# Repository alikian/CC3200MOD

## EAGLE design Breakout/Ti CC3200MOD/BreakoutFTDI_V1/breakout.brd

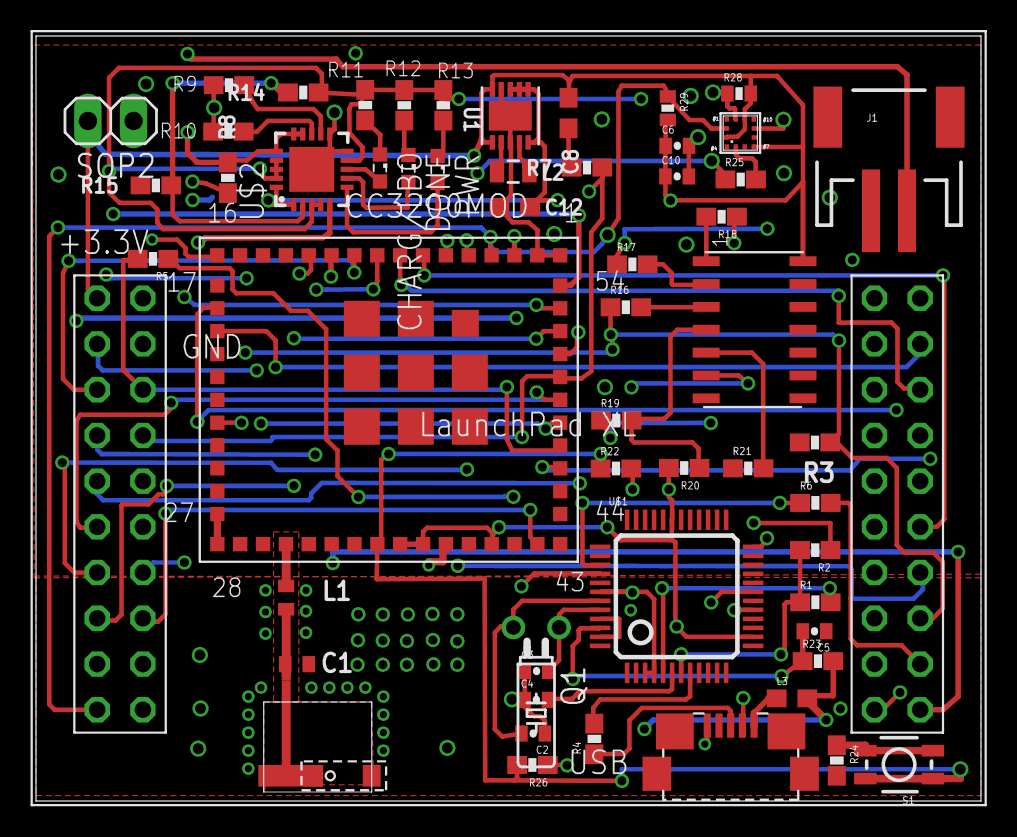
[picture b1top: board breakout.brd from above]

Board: 4 copper layers, 52.5 x 42.5 mm, 57 parts (1 on the bottom side), 66 nets.

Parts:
ANT_PAD: ANT
C1: 1pF; C0402
C2, C3: 27pF; 0402-CAP
C4: 33nF; 0402-CAP
C5: 0.1uF; 0402-CAP
C6, C10: .1uF; 0402-CAP
C8, C12: 10uF; C0603
CC3200MOD: CC3200; CC3200MOD
CHARG/LBO: SML0603
DONE: SML0603
J1: JST-2-SMD
L1: 3.6nH; C0402
L2: 2.2uH; 0805
L3: 0603
PWR: SML0603
Q1: 16Mhz; TC26H
R1: 1.5K; 0603-RES
R2, R4: 28; 0603-RES
R3: 2.7K; 0603-RES
R5, R6, R16, R17, R18, R19, R21, R22, R24: 33; 0603-RES
R7, R10, R26: 100K; 0603-RES
R8: 470K; 0603-RES
R9: 2K; 0603-RES
R11, R12, R13, R14, R15: 1K; 0603-RES
R20: 10k; 0603-RES
R23: 470; 0603-RES
R25: 0R; 0603-RES
R28, R29: 33K; 0402-RES
S1: TACTILE_SWITCH_SMD
SOP2: 1X02
THERMAL: 10K; 0603-RES
U1: TPS63001DRCT; SON50P300X300X100-11N
U11: XL; LAUNCHPADXL
U$1: FT2232D; LQFP-48
U$2: MCP73871-2CCI/ML; QFN20-4X4
U$3: DECADE-74LVC125A; DECADE-SO-14
U$4: BMA220; BMA222
USB: MICRO-USB-ZX62R-B-5P; ZX62R-B-5P

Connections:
+5V_USB: L3.2, R11.2, R12.2, R13.2, R14.2, R23.2, U$1.3, U$1.4, U$1.42, U$2.3, U$2.4, U$2.9, U$2.17, U$2.18, U$2.19
+BATT: J1.2, R8.2, U$2.14, U$2.15, U$2.16
DBGEN_N: R18.2, U$3.1
DBG_RST_N: R19.2, R20.1, U$3.4
FTDI_RX: CC3200MOD.P46, R6.2, U11.GPIO_01
FTDI_TX: CC3200MOD.P47, R5.2, U11.GPIO_02
FT_SK: R17.2, U$3.2
GND: ANT_PAD.ANT_GND, ANT_PAD.GND_LEFT, C1.2, C2.1, C3.1, C4.1, C5.1, C6.2, C8.2, C10.2, C12.2, CC3200MOD.P1, CC3200MOD.P2, CC3200MOD.P16, CC3200MOD.P27, CC3200MOD.P28, CC3200MOD.P30, CC3200MOD.P32, CC3200MOD.P38, CC3200MOD.P43, CC3200MOD.P55, CC3200MOD.P56, CC3200MOD.P57, CC3200MOD.P58, CC3200MOD.P59, CC3200MOD.P60, CC3200MOD.P61, CC3200MOD.P62, CC3200MOD.P63, J1.1, R3.2, R7.1, R9.1, R10.1, R15.1, R21.1, R24.2, THERMAL.1, U1.3, U1.9, U1.11, U11.GND1, U11.GND2, U$1.9, U$1.18, U$1.25, U$1.34, U$1.45, U$1.47, U$2.10, U$2.11, U$2.21, U$3.7, U$4.P1, U$4.P8, U$4.P9, USB.5
GPIO_05: CC3200MOD.P50, R7.2, R8.1, U11.GPIO_05
GPIO_10: CC3200MOD.P3, R28.1, U11.GPIO_10, U$4.P12
GPIO_11: CC3200MOD.P4, R29.1, U11.GPIO_11, U$4.P2
GPIO_13: CC3200MOD.P10, R25.1, U11.GPIO_13_RX
GPIO_22: CC3200MOD.P11, U11.GPIO_22
JTAG_TDI: CC3200MOD.P12, U11.GPIO_23
JTAG_TDO: CC3200MOD.P18, U11.GPIO_24
unnamed: ANT_PAD.FEED2, C1.1, L1.1
unnamed: CC3200MOD.P31, L1.2
unnamed: R1.2, U$1.5
unnamed: CC3200MOD.P6, U11.GPIO_15_MISO
unnamed: CC3200MOD.P7, U11.GPIO_16_MOSI
unnamed: CC3200MOD.P8, U11.GPIO_17_CS
unnamed: CC3200MOD.P5, U11.GPIO_14_SP_CLK
unnamed: CC3200MOD.P19, U11.GPIO_28
unnamed: CC3200MOD.P42, U11.GPIO_30
unnamed: L3.1, USB.1
unnamed: R9.2, U$2.12
unnamed: CC3200MOD.P51, U11.GPIO_06
unnamed: CC3200MOD.P49, U11.GPIO_04
unnamed: R10.2, U$2.13
unnamed: CC3200MOD.P52, U11.GPIO_07
unnamed: CC3200MOD.P53, U11.GPIO_08
unnamed: CC3200MOD.P54, U11.GPIO_09
unnamed: CC3200MOD.P9, U11.GPIO_12_TX
unnamed: PWR.A, U$2.6
unnamed: CC3200MOD.P48, U11.GPIO_03
unnamed: THERMAL.2, U$2.5
unnamed: L2.1, U1.4
unnamed: L2.2, U1.2
unnamed: DONE.A, U$2.7
unnamed: CHARG/LBO.A, U$2.8
unnamed: CHARG/LBO.C, R11.1
unnamed: DONE.C, R12.1
unnamed: PWR.C, R13.1
unnamed: R14.1, R15.2, U$2.2
unnamed: C2.2, Q1.2, U$1.43
unnamed: C3.2, Q1.1, U$1.44
unnamed: R4.1, USB.3
unnamed: R2.1, USB.2
unnamed: C4.2, U$1.6
unnamed: R5.1, U$1.40
unnamed: R6.1, U$1.39
unnamed: R17.1, U$1.24
unnamed: R19.1, U$1.19
unnamed: R18.1, U$1.17
unnamed: R21.2, U$3.5
unnamed: R22.2, U$3.6
unnamed: C5.2, R23.1, U$1.46
unnamed: R25.2, U$4.P5
unnamed: R24.1, S1.3, S1.4
N_RESET: CC3200MOD.P35, R22.1, R26.2, S1.1, S1.2, U11.RESET_OUT
OUT: C12.1, U1.5, U1.6, U1.7, U1.8, U$2.1, U$2.20
SOP2: CC3200MOD.P23, R3.1, R16.1, SOP2.1, U11.GPIO_25
TCK: R16.2, U$3.3
USB_DM: R4.2, U$1.8
USB_DP: R1.1, R2.2, U$1.7
VCC: C6.1, C8.1, C10.1, CC3200MOD.P36, CC3200MOD.P37, CC3200MOD.P40, R20.2, R26.1, R28.2, R29.2, SOP2.2, U1.1, U1.10, U11.3.3V, U$1.14, U$1.31, U$3.14, U$4.P3, U$4.P7, U$4.P11

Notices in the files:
parts and their libraries:
SparkFun-Passives: Licensing: CC v3.0 Share-Alike You are welcome to use this library for commercial purposes.
SparkFun-Connectors: Licensing: Creative Commons ShareAlike 4.0 International - https://creativecommons.org/licenses/by-sa/4.0
